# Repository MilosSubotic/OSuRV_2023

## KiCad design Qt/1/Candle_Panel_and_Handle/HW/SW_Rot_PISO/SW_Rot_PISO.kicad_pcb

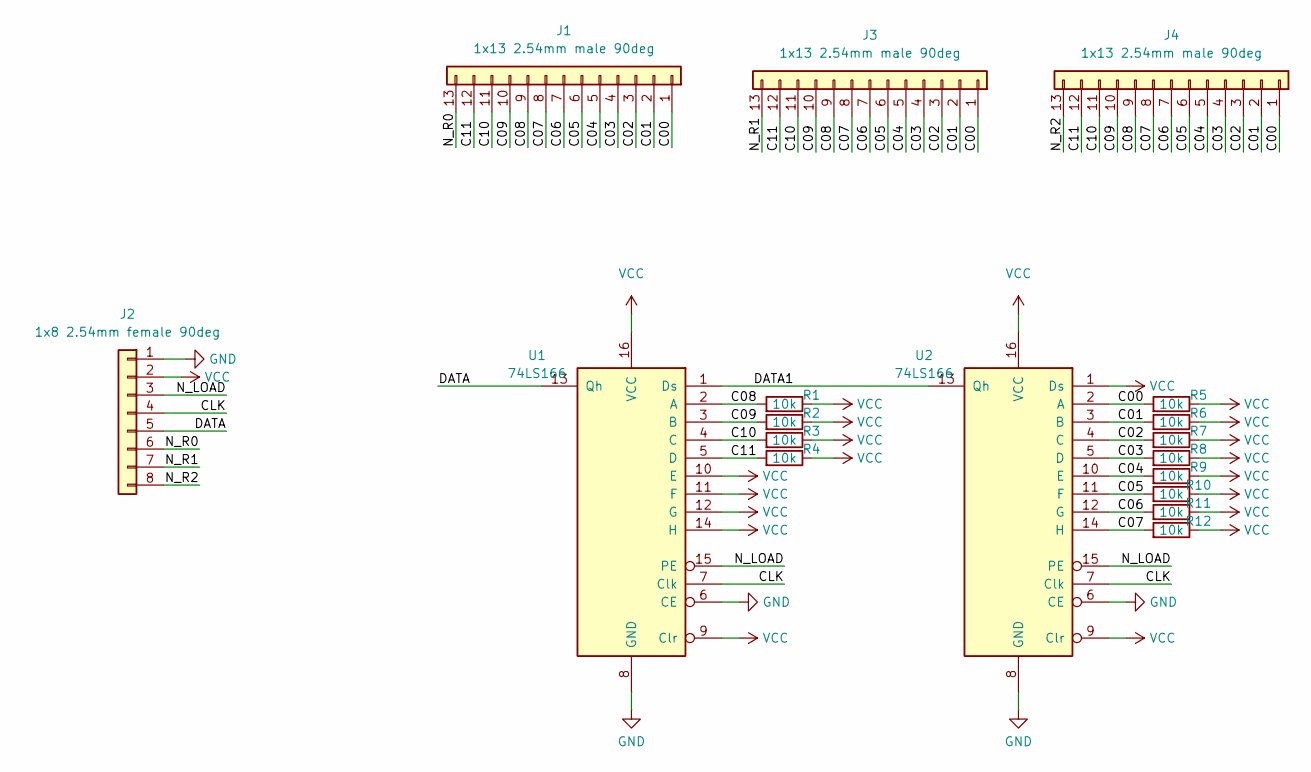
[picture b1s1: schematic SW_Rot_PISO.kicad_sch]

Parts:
J1, J3, J4: 1x13 2.54mm male 90deg; SW_Rot_1x12_Daughterbrd_Conn
J2: 1x8 2.54mm female 90deg; PinSocket_1x08_P2.54mm_Horizontal
R1, R2, R3, R4, R5, R6, R7, R8, R9, R10, R11, R12: 10k; R_Axial_DIN0207_L6.3mm_D2.5mm_P7.62mm_Horizontal
U1, U2: 74LS166; DIP-16_W7.62mm

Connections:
/C00: J1.1, J3.1, J4.1, R5.2, U2.2 (A)
/C01: J1.2, J3.2, J4.2, R6.2, U2.3 (B)
/C02: J1.3, J3.3, J4.3, R7.2, U2.4 (C)
/C03: J1.4, J3.4, J4.4, R8.2, U2.5 (D)
/C04: J1.5, J3.5, J4.5, R9.2, U2.10 (E)
/C05: J1.6, J3.6, J4.6, R10.2, U2.11 (F)
/C06: J1.7, J3.7, J4.7, R11.2, U2.12 (G)
/C07: J1.8, J3.8, J4.8, R12.2, U2.14 (H)
/C08: J1.9, J3.9, J4.9, R1.2, U1.2 (A)
/C09: J1.10, J3.10, J4.10, R2.2, U1.3 (B)
/C10: J1.11, J3.11, J4.11, R3.2, U1.4 (C)
/C11: J1.12, J3.12, J4.12, R4.2, U1.5 (D)
/CLK: J2.4, U1.7 (Clk), U2.7 (Clk)
/DATA: J2.5, U1.13 (Qh)
/DATA1: U1.1 (Ds), U2.13 (Qh)
/N_LOAD: J2.3, U1.15 (PE), U2.15 (PE)
/N_R0: J1.13, J2.6
/N_R1: J2.7, J3.13
/N_R2: J2.8, J4.13
GND: J2.1, U1.6 (CE), U1.8 (GND), U2.6 (CE), U2.8 (GND)
VCC: J2.2, R1.1, R2.1, R3.1, R4.1, R5.1, R6.1, R7.1, R8.1, R9.1, R10.1, R11.1, R12.1, U1.9 (Clr), U1.10 (E), U1.11 (F), U1.12 (G), U1.14 (H), U1.16 (VCC), U2.1 (Ds), U2.9 (Clr), U2.16 (VCC)

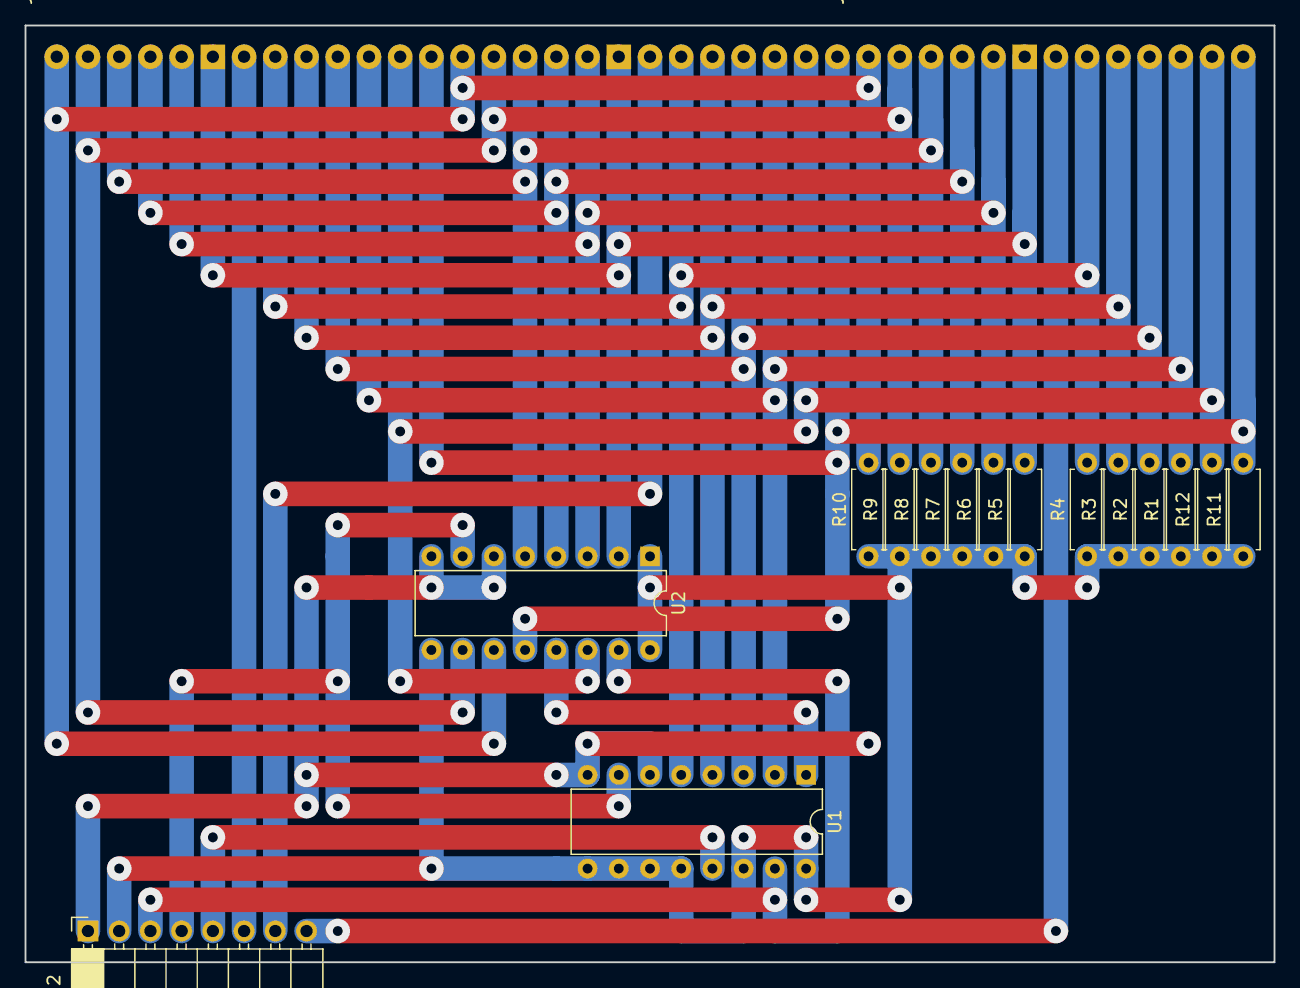
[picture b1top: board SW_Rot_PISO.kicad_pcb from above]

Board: 2 copper layers, 101.6 x 76.2 mm, 18 parts (1 on the bottom side), 21 nets.

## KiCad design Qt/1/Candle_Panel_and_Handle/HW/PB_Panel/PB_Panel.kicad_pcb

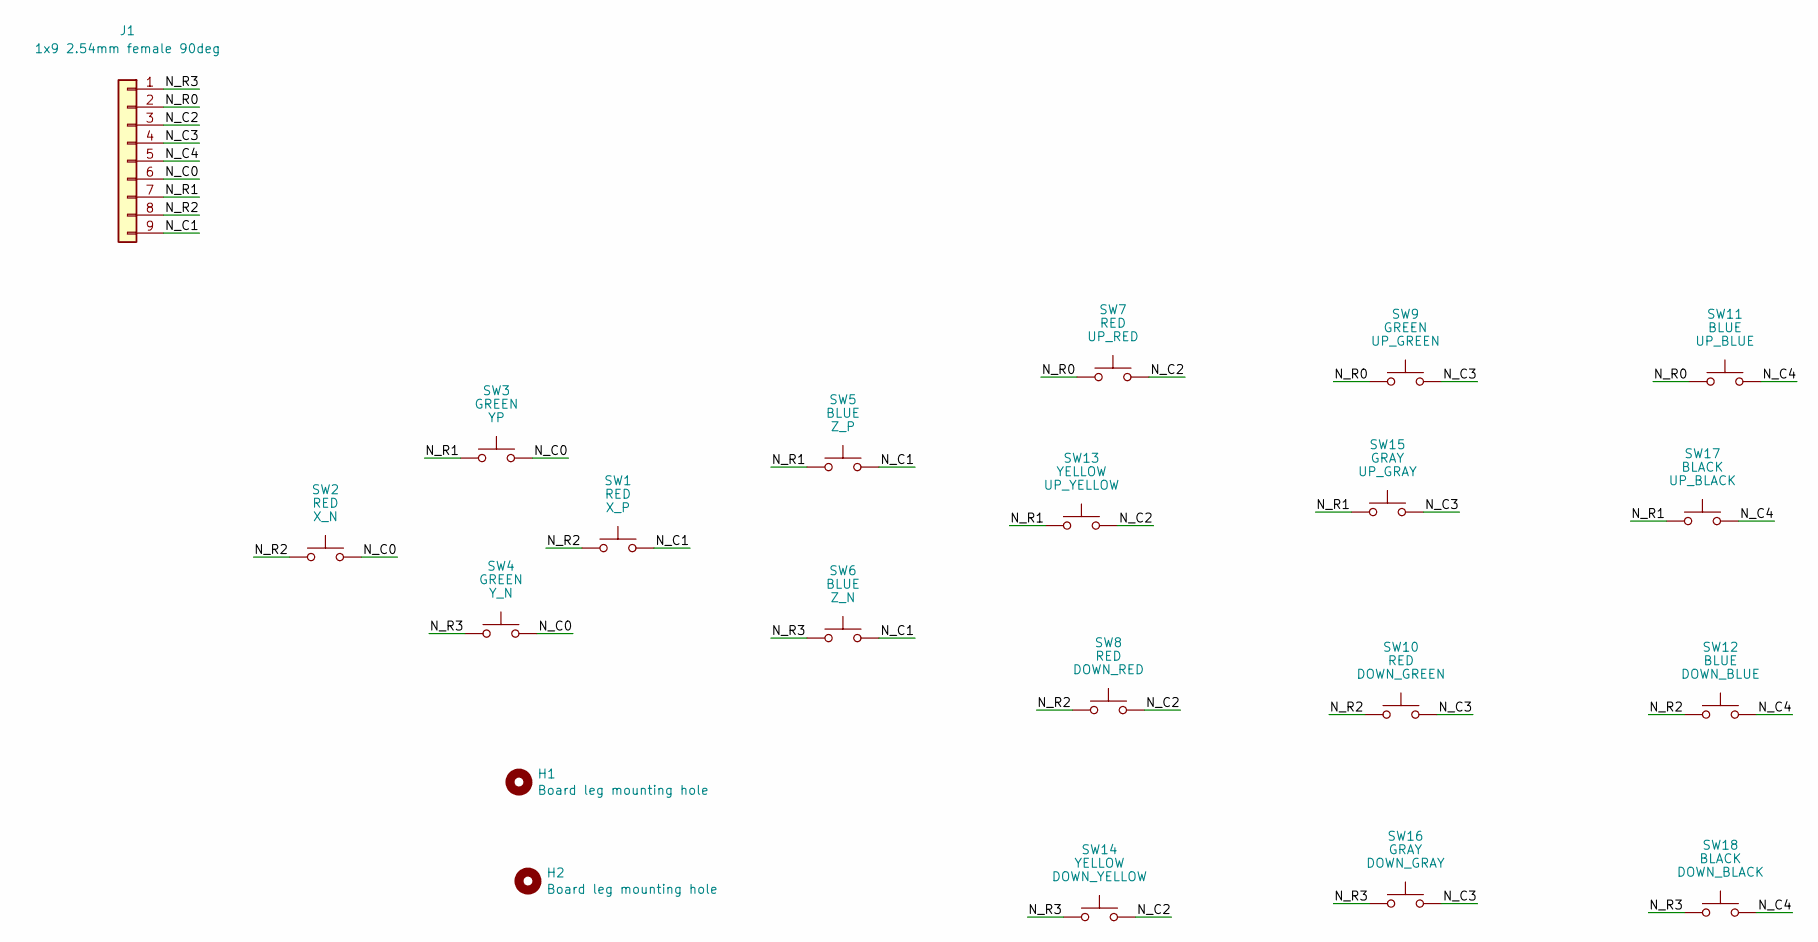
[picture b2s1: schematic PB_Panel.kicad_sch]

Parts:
H1, H2: Board leg mounting hole; MountingHole_3.2mm_M3
J1: 1x9 2.54mm female 90deg; PinSocket_1x09_P2.54mm_Horizontal
SW1, SW2, SW7, SW8, SW10: RED; SW_PUSH_Color_B9mm_D12mm_P5.08mm
SW3, SW4, SW9: GREEN; SW_PUSH_Color_B9mm_D12mm_P5.08mm
SW5, SW6, SW11, SW12: BLUE; SW_PUSH_Color_B9mm_D12mm_P5.08mm
SW13, SW14: YELLOW; SW_PUSH_Color_B9mm_D12mm_P5.08mm
SW15, SW16: GRAY; SW_PUSH_Color_B9mm_D12mm_P5.08mm
SW17, SW18: BLACK; SW_PUSH_Color_B9mm_D12mm_P5.08mm

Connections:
/N_C0: J1.6, SW2.1, SW3.1, SW4.1
/N_C1: J1.9, SW1.1, SW5.1, SW6.1
/N_C2: J1.3, SW7.1, SW8.1, SW13.1, SW14.1
/N_C3: J1.4, SW9.1, SW10.1, SW15.1, SW16.1
/N_C4: J1.5, SW11.1, SW12.1, SW17.1, SW18.1
/N_R0: J1.2, SW7.2, SW9.2, SW11.2
/N_R1: J1.7, SW3.2, SW5.2, SW13.2, SW15.2, SW17.2
/N_R2: J1.8, SW1.2, SW2.2, SW8.2, SW10.2, SW12.2
/N_R3: J1.1, SW4.2, SW6.2, SW14.2, SW16.2, SW18.2

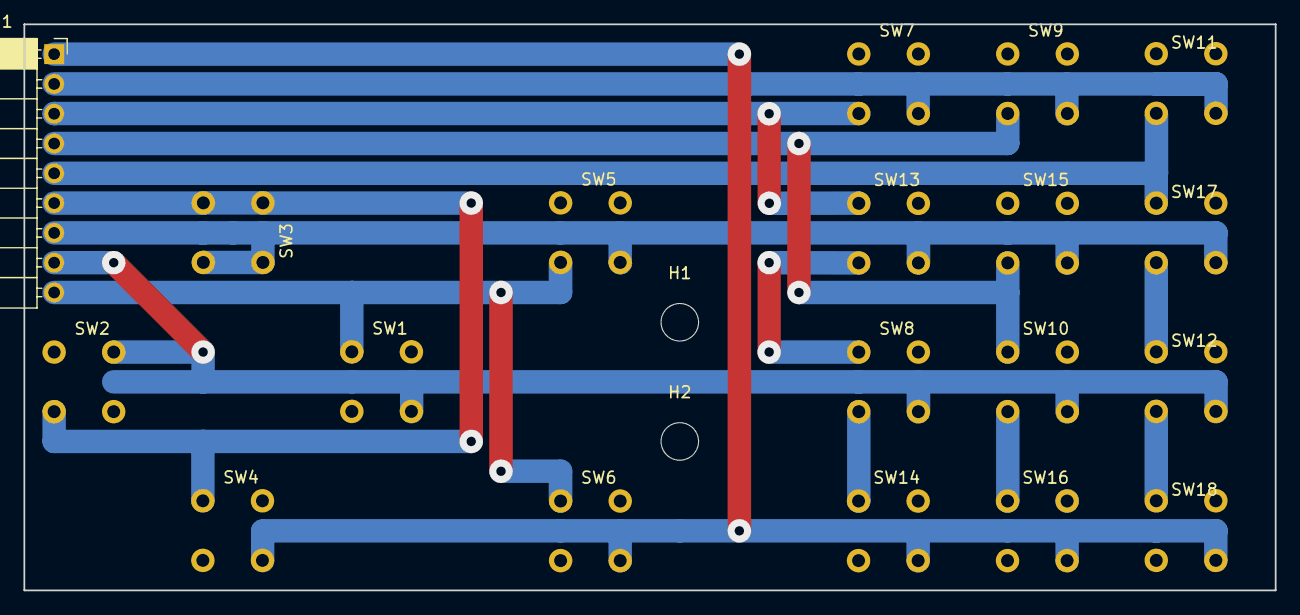
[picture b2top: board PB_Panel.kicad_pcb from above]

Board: 2 copper layers, 106.7 x 48.3 mm, 21 parts (0 on the bottom side), 9 nets.

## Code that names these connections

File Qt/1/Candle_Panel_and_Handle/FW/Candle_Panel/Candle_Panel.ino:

//Pins for rotary switches
int load=A0;
int clockPulse=A1;
int dataOut=A2;
int r0=A3;
int r1=A4;
int r2=A5;
int previous_position[] = {-1,-1,-1}; //Previous position of rotary switches

//Pins for buttons
int n_r0=3;
int n_r1=8;
int n_r2=9;
int n_r3=2;
int n_c0=7;  
int n_c1=10;
int n_c2=4;
int n_c3=5;
int n_c4=6;

int previous_matrix[4][5]={
  {1,1,1,1,1},
  {1,1,1,1,1},
  {1,1,1,1,1},
  {1,1,1,1,1}
};

//Messages to send via serial port when buttons is pressed
const String messages[4][5]={
  {"", "", "", "", ""},
  {"PANForward=", "PANJog_up=", "", "", ""},
  {"PANJog_left=", "PANJog_right=", "", "", ""},
  {"PANBackward=", "PANJog_down=", "", "", ""}
};

uint16_t value;

void setup(){
  pinMode(load, OUTPUT);
  pinMode(clockPulse, OUTPUT);
  pinMode(dataOut, INPUT);
  pinMode(r2, INPUT);
  pinMode(r1, INPUT);
  pinMode(r0, INPUT);
  
  pinMode(n_r0, INPUT);
  pinMode(n_r1, INPUT);
  pinMode(n_r2, INPUT);
  pinMode(n_r3, INPUT);
  pinMode(n_c0, INPUT_PULLUP);
  pinMode(n_c1, INPUT_PULLUP);
  pinMode(n_c2, INPUT_PULLUP);
  pinMode(n_c3, INPUT_PULLUP);
  pinMode(n_c4, INPUT_PULLUP); 
  
  Serial.begin(115200);
}

void loop(){
    pinMode(r2, OUTPUT);
    digitalWrite(r2, 0);
    readF(2);
   

   pinMode(r2, INPUT);
    pinMode(r1, OUTPUT);
    digitalWrite(r2, 1);
    digitalWrite(r1, 0);
    readF(1);
    pinMode(r1, INPUT);
    pinMode(r0, OUTPUT);
    digitalWrite(r1, 1);
    digitalWrite(r0, 0);
    readF(0);
    pinMode(r0, INPUT);
    digitalWrite(r0, 1);


    for(int i = 0; i < 4; i++){
       selectButton(i);
       //delay(50);
    }
}

void selectButton(int row){
  
  switch(row){
    case 0:
      pinMode(n_r0, OUTPUT);
      digitalWrite(n_r0, LOW);
      readButton(0);
      pinMode(n_r0, INPUT);
      break;
    case 1:
      pinMode(n_r1, OUTPUT);
      digitalWrite(n_r1, LOW);
      readButton(1);
      pinMode(n_r1, INPUT);
      break;
    case 2:
      pinMode(n_r2, OUTPUT);
      digitalWrite(n_r2, LOW);
      readButton(2);
      pinMode(n_r2, INPUT);
      break;
    case 3:
      pinMode(n_r3, OUTPUT);
      digitalWrite(n_r3, LOW);
      readButton(3);
      pinMode(n_r3, INPUT);
      break;
  }
}

void readButton(int row){
    int read_n_c0 = digitalRead(n_c0);
    if(read_n_c0!=previous_matrix[row][0]){
      Serial.println(messages[row][0]+previous_matrix[row][0]);
      previous_matrix[row][0]=read_n_c0;
    }
    int read_n_c1 = digitalRead(n_c1);
    if(read_n_c1!=previous_matrix[row][1]){
      Serial.println(messages[row][1]+previous_matrix[row][1]);
      previous_matrix[row][1]=read_n_c1;
    }
    int read_n_c2 = digitalRead(n_c2);
    if(read_n_c2!=previous_matrix[row][2]){
      Serial.println(messages[row][2]+previous_matrix[row][2]);
      previous_matrix[row][2]=read_n_c2;
    }
    int read_n_c3 = digitalRead(n_c3);
    if(read_n_c3!=previous_matrix[row][3]){
      Serial.println(messages[row][3]+previous_matrix[row][3]);
      previous_matrix[row][3]=read_n_c3;
    }
   int read_n_c4 = digitalRead(n_c4);
    if(read_n_c4!=previous_matrix[row][4]){
      Serial.println(messages[row][4]+previous_matrix[row][4]);
      previous_matrix[row][4]=read_n_c4;
    }
}

void readF(int sw){
    uint16_t dataIn=0;
    int position=-1;
    digitalWrite(clockPulse, 0);
    digitalWrite(load, 0);
    delay(1);
    digitalWrite(clockPulse, 0);
  
    delay(1);
    digitalWrite(clockPulse, 1);
    delay(1);
    digitalWrite(load, 1);
    
    delay(1);
   
    for(int j=15; j>=0; j--){
      digitalWrite(clockPulse, 1);
      delay(1);
      value=digitalRead(dataOut);
      if(value){
        int a=(1 << j);
        
        dataIn=dataIn | a;
      } 
      else{
           position=j;
      }
     
       digitalWrite(clockPulse, 0); 
       delay(1);
    }
 // Serial.println(dataIn, BIN);
    if(previous_position[sw]==-1)
      previous_position[sw]=position;
    
    if(previous_position[sw] != position){
      if(sw == 1){
        if(previous_position[sw] > position){
          Serial.println("PANJog_rate_next=1");
        }else{
          Serial.println("PANJog_rate_previous=1"); 
        }
      }else if(sw == 2){
        if(previous_position[sw] > position){
          Serial.println("PANJog_feed_next=1");
        }else{
          Serial.println("PANJog_feed_previous=1"); 
        }
      }
      previous_position[sw] = position;
    }
    delay(1);

    digitalWrite(clockPulse, 1);
    
    delay(25);
}

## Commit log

2023-11-20 Common.
2023-12-12 For tank chassis.
2023-12-13 No need for this.
2023-12-13 Install Candle.
2023-12-13 s4a prj resources.
2023-12-19 Added lab 7 and joy_node.cpp as test_joypad.cpp to applications.
2023-12-19 Added flow.sh
2023-12-20 Dokumentacija - V1
    new file: v1_notes.txt
    author: Aleksa Djurdjevic
    email: aleksadjurdjevic015@gmail.com
2023-12-23 dodat libenjoy_linux.c i libenjoy_linux.h u SW/Test/test_app
2023-12-28 Vezba2
2023-12-28 dodato sa ovonedeljnih vezbi
2024-01-11 test_chassis.c i prosirena dokumentacija
2024-01-17 Finalno(possibly)
2024-01-19 Napravljena testnaaplikacija
2024-01-19 profesor milos izmenio tmuxer
2024-01-19 ispravljen tmuxer
2024-01-19 izmenjena testna aplikacija, prosirena dokumentacija
